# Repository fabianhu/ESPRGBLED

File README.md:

# ESPRGBLED
RGB LED driver with 3 N-channel MOSFET drivers and an ESP8266

This is a small hardware board to drive a RGB LED or stripe with a ESP8266 ESP-12e module.

The folder /ESP8266 contains a caller monitor script for the fritz box:
- lights red on incoming call
- green for connected
- blue for outgoing

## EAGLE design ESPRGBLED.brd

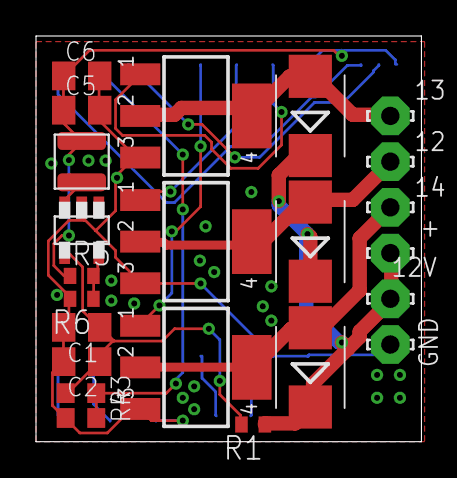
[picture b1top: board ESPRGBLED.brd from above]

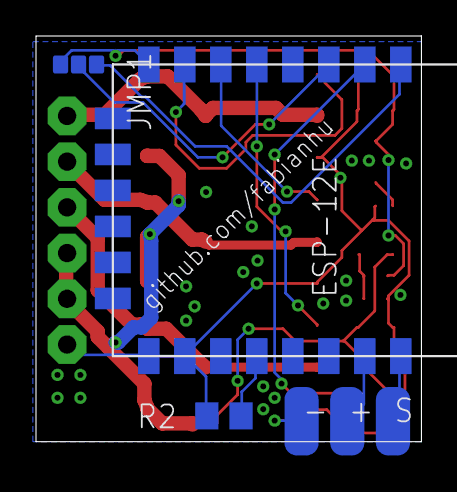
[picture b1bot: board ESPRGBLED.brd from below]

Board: 2 copper layers, 21.4 x 22.5 mm, 27 parts (4 on the bottom side), 18 nets.

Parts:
12, 12V, 13, 14: LSP10
+: LSP10
C1, C2, C5, C6: 10uF; C0805K
GND: LSP10
JMP1: 0R-JUMPC; C0R-JMP
L1: L_10UH_560MA; TYS3010100M-10
MDL1: ESP8266-ESP12E
PWR1:D1, PWR2:D1, PWR3:D1: MBRS130LT3; SMB
PWR1:T1, PWR2:T1, PWR3:T1: SOT223
R1: 0R; R0402
R2: 0R; R0805
R3: 100k; R0603
R4: 10k; R0603
R5: 61k9; R0402
R6: 20k; R0402
U$2: TPS560200; SOT23-5
U$3: 3-WIRE_CONN

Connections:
+12V: 12V.MP, +.MP, PWR1:D1.C, PWR2:D1.C, PWR3:D1.C, R1.1
ADC: MDL1.2, R3.1, R4.2
CH_PD: JMP1.2, MDL1.3
GND: C1.2, C2.2, C5.2, C6.2, GND.MP, MDL1.9, MDL1.10, PWR1:T1.3, PWR2:T1.3, PWR3:T1.3, R2.2, R4.1, R6.2, U$2.2, U$3.0V
GPIO0: MDL1.12, R2.1
GPIO12: MDL1.6, PWR2:T1.1
GPIO13: MDL1.7, PWR1:T1.1
GPIO14: MDL1.5, PWR3:T1.1
unnamed: 13.MP, PWR1:D1.A, PWR1:T1.2, PWR1:T1.4
unnamed: 12.MP, PWR2:D1.A, PWR2:T1.2, PWR2:T1.4
unnamed: 14.MP, PWR3:D1.A, PWR3:T1.2, PWR3:T1.4
unnamed: MDL1.16, U$3.SIG
unnamed: MDL1.15, U$3.5V
unnamed: L1.P$1, U$2.3
unnamed: R5.2, R6.1, U$2.5
REST: JMP1.1, MDL1.1
VCC: C5.1, C6.1, JMP1.3, L1.P$2, MDL1.8, R5.1
VIN: C1.1, C2.1, R1.2, R3.2, U$2.4

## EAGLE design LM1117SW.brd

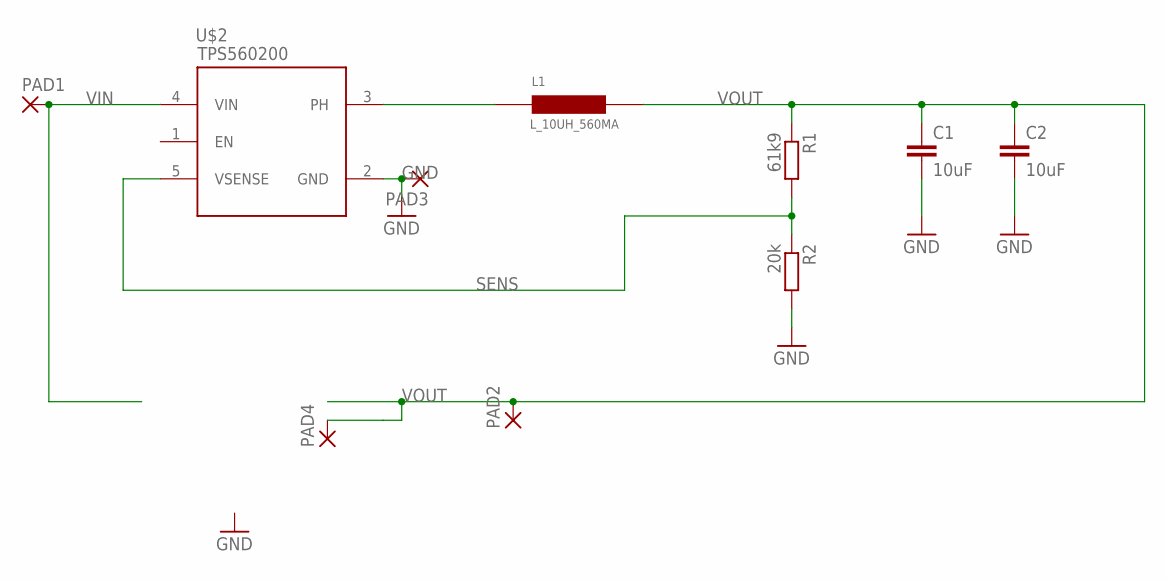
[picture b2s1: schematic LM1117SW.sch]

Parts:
C1, C2: 10uF; C0805K; MPN MC0805X106K250CT
L1: L_10UH_560MA; TYS3010100M-10; MPN TYS3010100M-10
PAD1, PAD2, PAD3, PAD4: 1,6/0,9
R1: 61k9; R0402; MPN MC00625W0402161K9
R2: 20k; R0402; MPN CRCW040220K0FKED
U$2: TPS560200; SOT23-5; MPN TPS560200DBVT

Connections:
GND: C1.2, C2.2, PAD3.1, R2.2, U$2.2 (GND)
unnamed: L1.P$1, U$2.3 (PH)
SENS: R1.2, R2.1, U$2.5 (VSENSE)
VIN: PAD1.1, U$2.4 (VIN)
VOUT: C1.1, C2.1, L1.P$2, PAD2.1, PAD4.1, R1.1

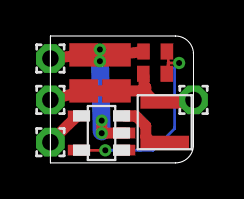
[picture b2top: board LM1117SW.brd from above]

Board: 2 copper layers, 8.0 x 7.0 mm, 10 parts (0 on the bottom side), 5 nets.

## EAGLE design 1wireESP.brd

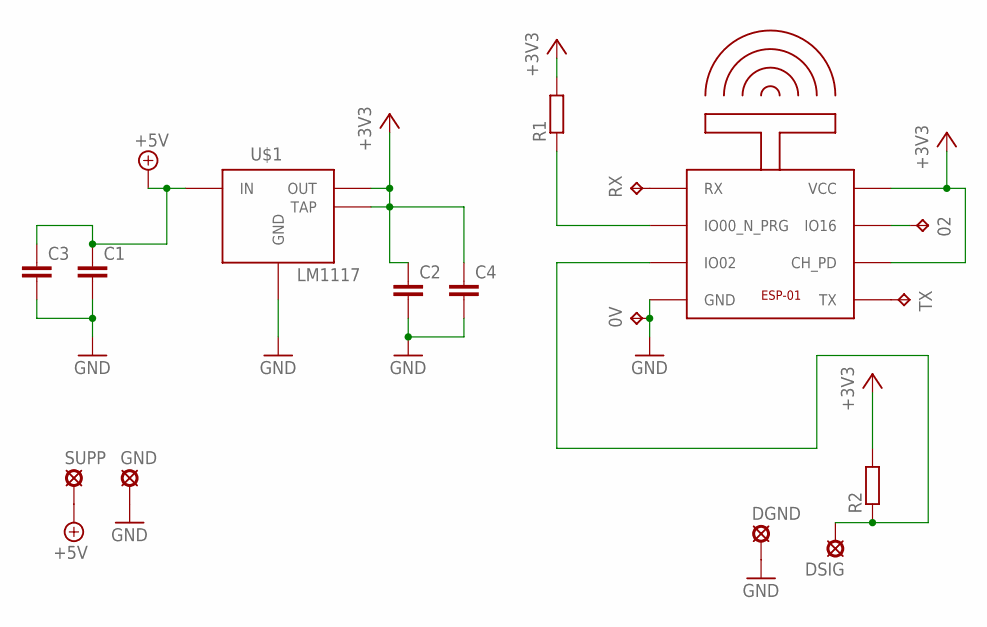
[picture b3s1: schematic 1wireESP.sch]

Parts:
0V, 02: TPB2,54; B2,54
C1, C2: C-EUC0603K; C0603K
C3, C4: C-EUC0805K; C0805K
DGND: LSP10
DSIG: LSP10
GND: LSP10
R1, R2: R-EU_R0603; R0603
RX: TPB2,54; B2,54
SUPP: LSP10
TX: TPB2,54; B2,54
U$1: LM1117; SOT223
U$2: ESP-01

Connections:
+3V3: C2.1, C4.1, R1.2, R2.2, U$1.MID (OUT), U$1.TAP, U$2.CH_PD, U$2.VCC
+5V: C1.1, C3.1, SUPP.MP, U$1.RIGHT (IN)
GND: 0V.TP, C1.2, C2.2, C3.2, C4.2, DGND.MP, GND.MP, U$1.LEFT (GND), U$2.GND
unnamed: R1.1, U$2.GPIO0_N_PROG (IO00_N_PRG)
unnamed: 02.TP, U$2.GPIO16 (IO16)
unnamed: DSIG.MP, R2.1, U$2.GPIO02 (IO02)
unnamed: TX.TP, U$2.TX
unnamed: RX.TP, U$2.RX

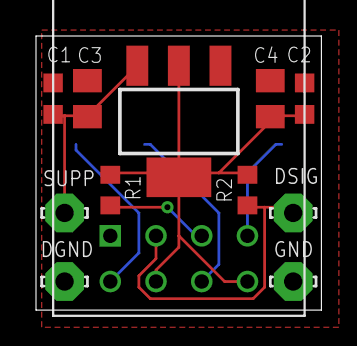
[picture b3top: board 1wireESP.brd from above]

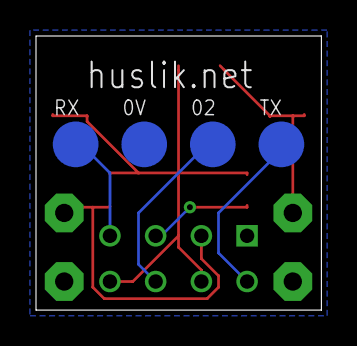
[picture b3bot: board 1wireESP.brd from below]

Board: 2 copper layers, 15.9 x 15.2 mm, 16 parts (4 on the bottom side), 8 nets.

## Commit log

2015-06-21 initial stuff
2015-06-23 added layout
2015-06-23 layouted
2015-07-04 updated layouts
2015-07-12 through hole
2015-07-12 minor stuff
2015-07-18 updated HW with reset-wakeup option
2015-07-31 added image
2015-08-02 updated BOM
2015-08-06 minor layout stuff
2015-08-10 added esp
2015-08-10 first working over http
2015-08-15 updated schematics with step down vreg
2015-08-16 layout stuff
2015-08-16 finished LM1117 replacement
2015-08-16 updated order list
2015-08-17 removed lm1117
2015-09-27 add fritz caller monitor code
    tested with fritz box 7490
2015-09-27 added fritz init
2015-10-07 made fritz dim
2015-10-08 fix blinki
2015-10-08 fix connection loss
2015-10-11 superminiaturized
2015-11-29 added newest version of nodemcu
2015-12-07 add wol.lua
2015-12-07 cleaned
2015-12-09 beautified
